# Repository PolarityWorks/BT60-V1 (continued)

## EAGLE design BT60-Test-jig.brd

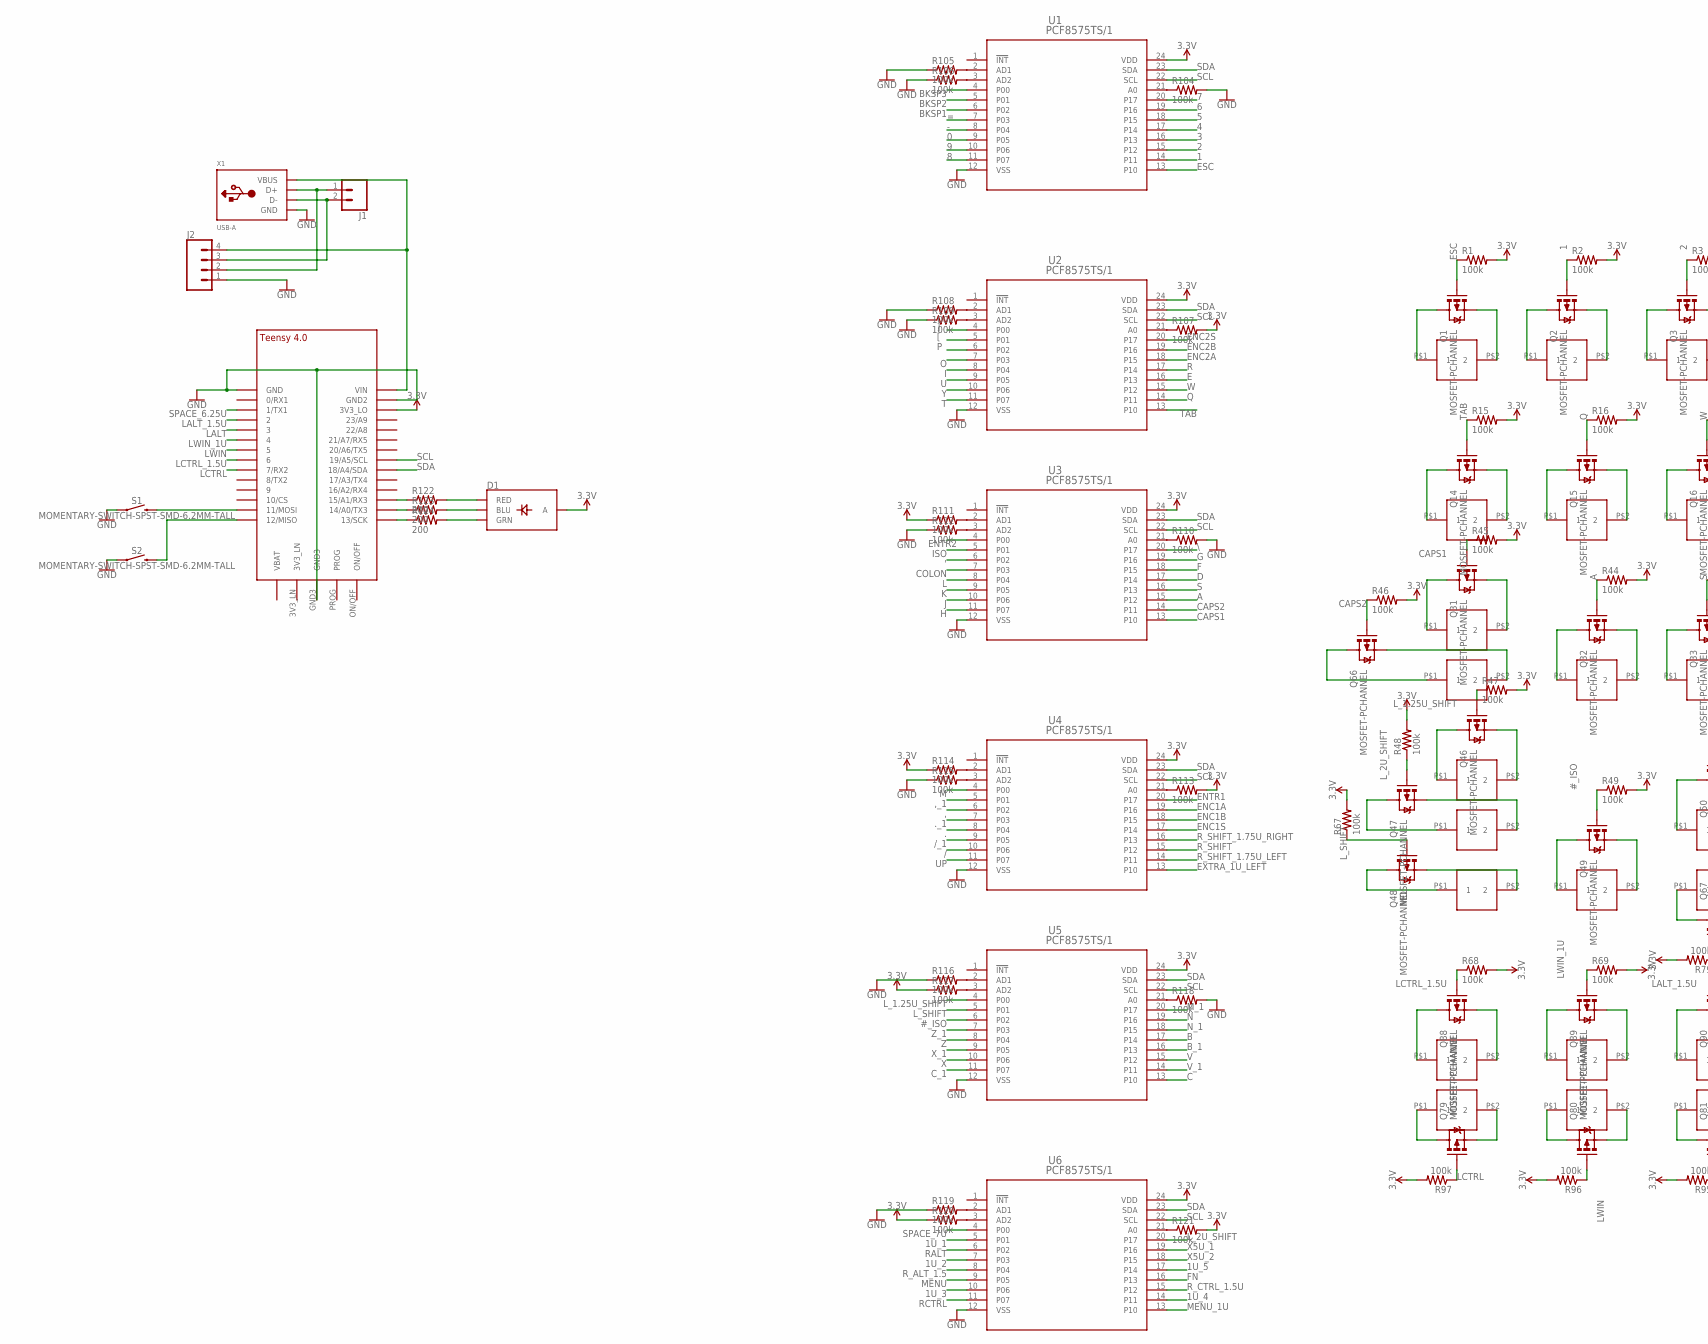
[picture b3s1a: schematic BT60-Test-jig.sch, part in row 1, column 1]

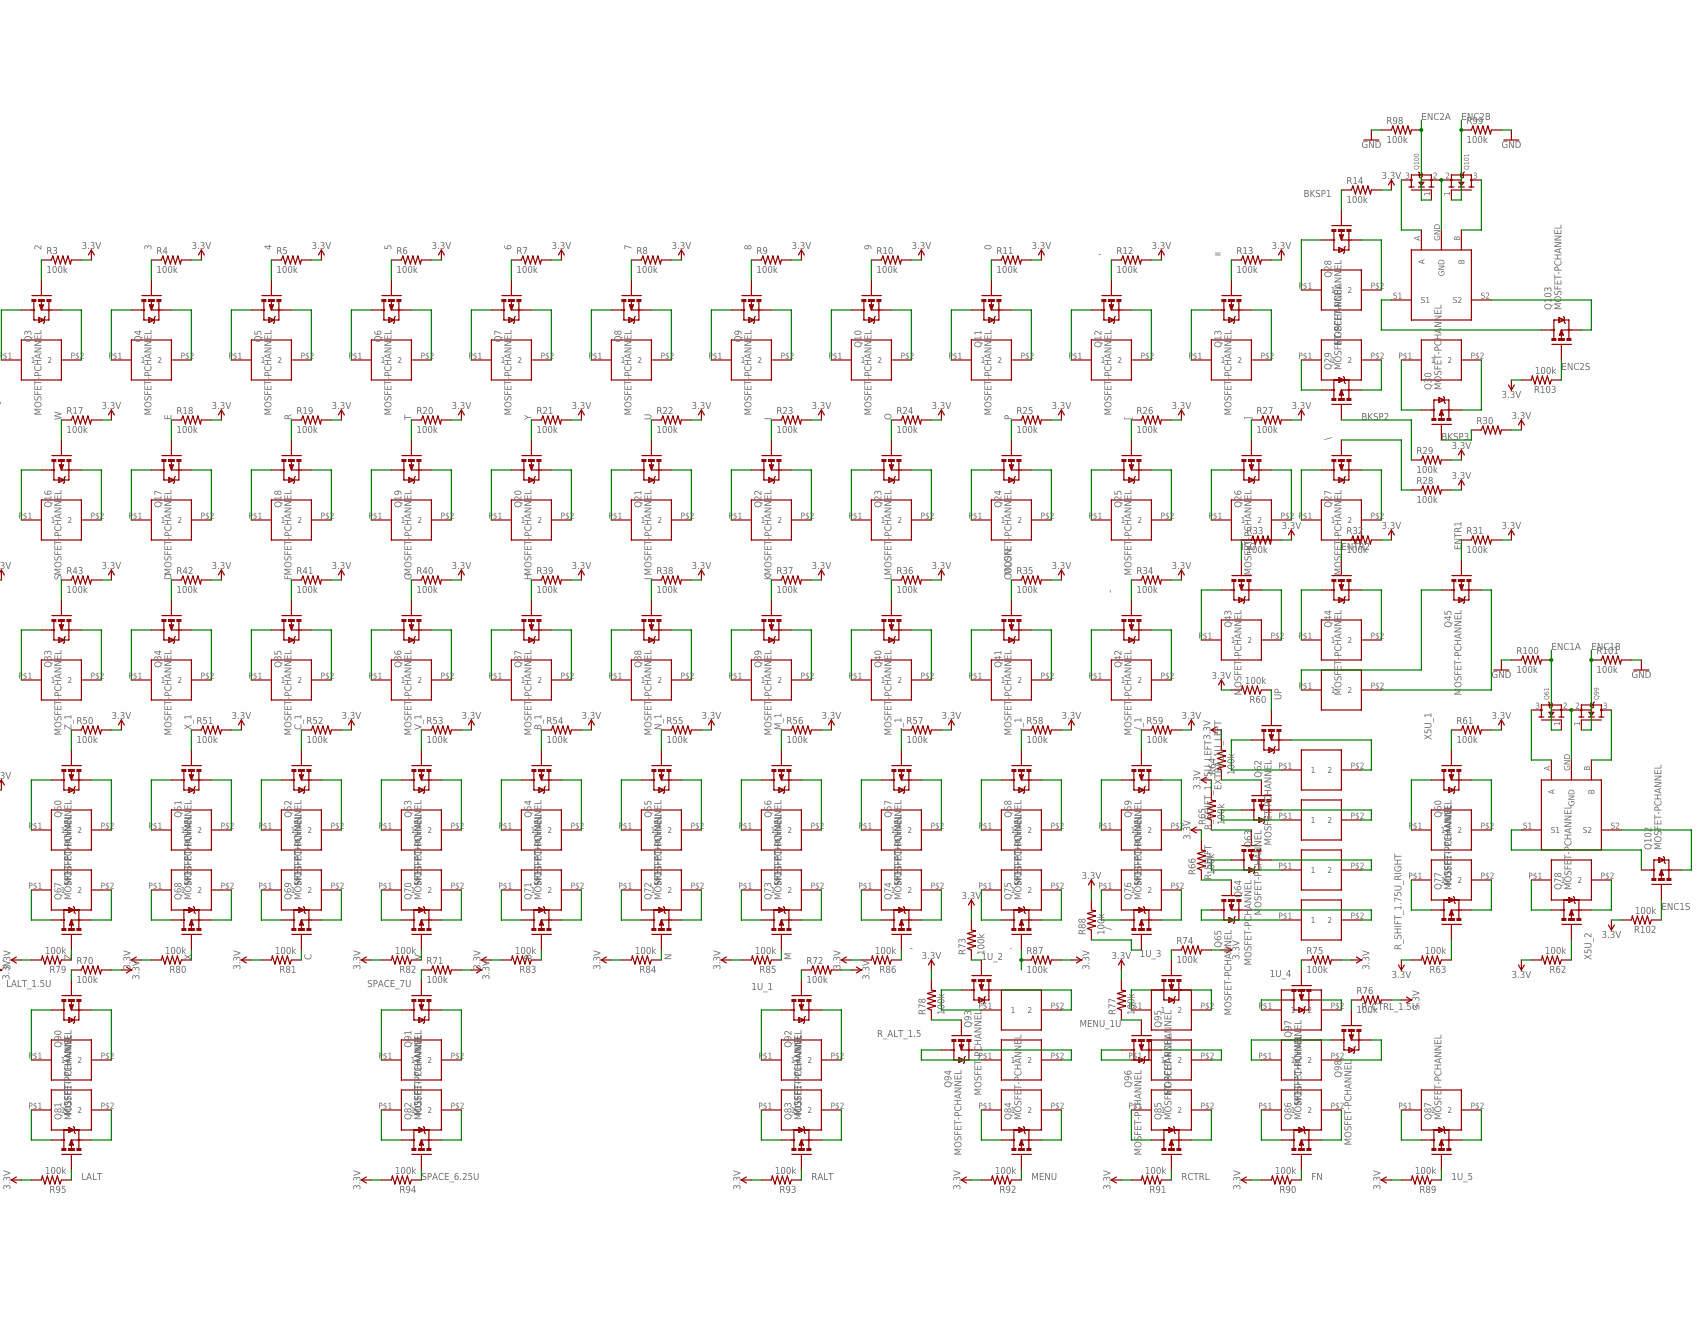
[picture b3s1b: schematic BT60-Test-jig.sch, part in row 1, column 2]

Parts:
0, 1, 1U_1, 1U_2, 1U_3, 1U_4, 1U_5, 2, 3, 4, 5, 6, 7, 8, 9, ., ._1: CHERRY-SOLDERCHERRY-TEST; CHERRY-TEST
#_ISO: CHERRY-SOLDERCHERRY-TEST; CHERRY-TEST
': CHERRY-SOLDERCHERRY-TEST; CHERRY-TEST
,: CHERRY-SOLDERCHERRY-TEST; CHERRY-TEST
,_1: CHERRY-SOLDERCHERRY-TEST; CHERRY-TEST
-: CHERRY-SOLDERCHERRY-TEST; CHERRY-TEST
/: CHERRY-SOLDERCHERRY-TEST; CHERRY-TEST
/_1: CHERRY-SOLDERCHERRY-TEST; CHERRY-TEST
=: CHERRY-SOLDERCHERRY-TEST; CHERRY-TEST
A: CHERRY-SOLDERCHERRY-TEST; CHERRY-TEST
B: CHERRY-SOLDERCHERRY-TEST; CHERRY-TEST
BS: CHERRY-SOLDERCHERRY-TEST; CHERRY-TEST
B_1: CHERRY-SOLDERCHERRY-TEST; CHERRY-TEST
C: CHERRY-SOLDERCHERRY-TEST; CHERRY-TEST
CAPS: CHERRY-SOLDERCHERRY-TEST; CHERRY-TEST
CAPS_STEP: CHERRY-SOLDERCHERRY-TEST; CHERRY-TEST
COLON: CHERRY-SOLDERCHERRY-TEST; CHERRY-TEST
C_1: CHERRY-SOLDERCHERRY-TEST; CHERRY-TEST
D: CHERRY-SOLDERCHERRY-TEST; CHERRY-TEST
D1: LED-RGB-CASMD; LED-TRICOLOR-SMD
E: CHERRY-SOLDERCHERRY-TEST; CHERRY-TEST
ENTER: CHERRY-SOLDERCHERRY-TEST; CHERRY-TEST
ESC: CHERRY-SOLDERCHERRY-TEST; CHERRY-TEST
EXTRA_1U_LEFT: CHERRY-SOLDERCHERRY-TEST; CHERRY-TEST
F: CHERRY-SOLDERCHERRY-TEST; CHERRY-TEST
FN: CHERRY-SOLDERCHERRY-TEST; CHERRY-TEST
G: CHERRY-SOLDERCHERRY-TEST; CHERRY-TEST
H: CHERRY-SOLDERCHERRY-TEST; CHERRY-TEST
I: CHERRY-SOLDERCHERRY-TEST; CHERRY-TEST
ISO_#: CHERRY-SOLDERCHERRY-TEST; CHERRY-TEST
ISO_ENTER: CHERRY-SOLDERCHERRY-TEST; CHERRY-TEST
J: CHERRY-SOLDERCHERRY-TEST; CHERRY-TEST
J1: CONN_02; 1X02
J2: CONN_041X04_NO_SILK; 1X04_NO_SILK
K: CHERRY-SOLDERCHERRY-TEST; CHERRY-TEST
L: CHERRY-SOLDERCHERRY-TEST; CHERRY-TEST
LALT: CHERRY-SOLDERCHERRY-TEST; CHERRY-TEST
LALT_1.5U: CHERRY-SOLDERCHERRY-TEST; CHERRY-TEST
LCTRL: CHERRY-SOLDERCHERRY-TEST; CHERRY-TEST
LCTRL_1.5U: CHERRY-SOLDERCHERRY-TEST; CHERRY-TEST
LWIN: CHERRY-SOLDERCHERRY-TEST; CHERRY-TEST
LWIN_1U: CHERRY-SOLDERCHERRY-TEST; CHERRY-TEST
L_1.25U_SHIFT, L_2U_SHIFT: CHERRY-SOLDERCHERRY-TEST; CHERRY-TEST
L_SHIFT: CHERRY-SOLDERCHERRY-TEST; CHERRY-TEST
M: CHERRY-SOLDERCHERRY-TEST; CHERRY-TEST
MENU: CHERRY-SOLDERCHERRY-TEST; CHERRY-TEST
MENU_1U: CHERRY-SOLDERCHERRY-TEST; CHERRY-TEST
M_1: CHERRY-SOLDERCHERRY-TEST; CHERRY-TEST
N: CHERRY-SOLDERCHERRY-TEST; CHERRY-TEST
N_1: CHERRY-SOLDERCHERRY-TEST; CHERRY-TEST
O: CHERRY-SOLDERCHERRY-TEST; CHERRY-TEST
P: CHERRY-SOLDERCHERRY-TEST; CHERRY-TEST
Q: CHERRY-SOLDERCHERRY-TEST; CHERRY-TEST
Q1, Q2, Q3, Q4, Q5, Q6, Q7, Q8, Q9, Q10, Q11, Q12, Q13, Q14, Q15, Q16, Q17, Q18, Q19, Q20, Q21, Q22, Q23, Q24, Q25, Q26, Q27, Q28, Q29, Q30, Q31, Q32, Q33, Q34, Q35, Q36, Q37, Q38, Q39, Q40, Q41, Q42, Q43, Q44, Q45, Q46, Q47, Q48, Q49, Q50, Q51, Q52, Q53, Q54, Q55, Q56, Q57, Q58, Q59, Q60, Q62, Q63, Q64, Q65, Q66, Q67, Q68, Q69, Q70, Q71, Q72, Q73, Q74, Q75, Q76, Q77, Q78, Q79, Q80, Q81, Q82, Q83, Q84, Q85, Q86, Q87, Q88, Q89, Q90, Q91, Q92, Q93, Q94, Q95, Q96, Q97, Q98, Q102, Q103: MOSFET-PCHANNEL; SOT23-3
Q61, Q99, Q100, Q101: MOSFET-NREFLOW; SOT23
R: CHERRY-SOLDERCHERRY-TEST; CHERRY-TEST
R1, R2, R3, R4, R5, R6, R7, R8, R9, R10, R11, R12, R13, R14, R15, R16, R17, R18, R19, R20, R21, R22, R23, R24, R25, R26, R27, R28, R29, R30, R31, R32, R33, R34, R35, R36, R37, R38, R39, R40, R41, R42, R43, R44, R45, R46, R47, R48, R49, R50, R51, R52, R53, R54, R55, R56, R57, R58, R59, R60, R61, R62, R63, R64, R65, R66, R67, R68, R69, R70, R71, R72, R73, R74, R75, R76, R77, R78, R79, R80, R81, R82, R83, R84, R85, R86, R87, R88, R89, R90, R91, R92, R93, R94, R95, R96, R97, R98, R99, R100, R101, R102, R103, R104, R105, R106, R107, R108, R109, R110, R111, R112, R113, R114, R115, R116, R117, R118, R119, R120, R121: 100k; 0603-R
R122, R123, R124: 200; 0603-R
RALT: CHERRY-SOLDERCHERRY-TEST; CHERRY-TEST
RCTRL: CHERRY-SOLDERCHERRY-TEST; CHERRY-TEST
R_ALT_1.5: CHERRY-SOLDERCHERRY-TEST; CHERRY-TEST
R_CTRL_1.5U: CHERRY-SOLDERCHERRY-TEST; CHERRY-TEST
R_SHIFT: CHERRY-SOLDERCHERRY-TEST; CHERRY-TEST
R_SHIFT_1.75U_LEFT, R_SHIFT_1.75U_RIGHT: CHERRY-SOLDERCHERRY-TEST; CHERRY-TEST
S: CHERRY-SOLDERCHERRY-TEST; CHERRY-TEST
S1, S2: MOMENTARY-SWITCH-SPST-SMD-6.2MM-TALL; TACTILE_SWITCH_SMD_6.2MM_TALL
SPACE_6.25U, SPACE_7U: CHERRY-SOLDERCHERRY-TEST; CHERRY-TEST
SPLIT_BS_1, SPLIT_BS_2: CHERRY-SOLDERCHERRY-TEST; CHERRY-TEST
T: CHERRY-SOLDERCHERRY-TEST; CHERRY-TEST
TAB: CHERRY-SOLDERCHERRY-TEST; CHERRY-TEST
U: CHERRY-SOLDERCHERRY-TEST; CHERRY-TEST
U1, U2, U3, U4, U5, U6: PCF8575TS/1; SOT340-1_NXP
U$1, U$3: ENCODER
U$2: TEENSY_4.0
UP: CHERRY-SOLDERCHERRY-TEST; CHERRY-TEST
V: CHERRY-SOLDERCHERRY-TEST; CHERRY-TEST
V_1: CHERRY-SOLDERCHERRY-TEST; CHERRY-TEST
W: CHERRY-SOLDERCHERRY-TEST; CHERRY-TEST
X, X5U_1, X5U_2: CHERRY-SOLDERCHERRY-TEST; CHERRY-TEST
X1: USB-A; MOLEX_480371000
X_1: CHERRY-SOLDERCHERRY-TEST; CHERRY-TEST
Y: CHERRY-SOLDERCHERRY-TEST; CHERRY-TEST
Z: CHERRY-SOLDERCHERRY-TEST; CHERRY-TEST
Z_1: CHERRY-SOLDERCHERRY-TEST; CHERRY-TEST
[: CHERRY-SOLDERCHERRY-TEST; CHERRY-TEST
\: CHERRY-SOLDERCHERRY-TEST; CHERRY-TEST
]: CHERRY-SOLDERCHERRY-TEST; CHERRY-TEST

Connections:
0: Q11.1 (G), R11.1, U1.9 (P05)
1: Q2.1 (G), R2.1, U1.14 (P11)
1U_1: Q92.1 (G), R72.1, U6.5 (P01)
1U_2: Q93.1 (G), R73.1, U6.7 (P03)
1U_3: Q95.1 (G), R74.1, U6.10 (P06)
1U_4: Q97.1 (G), R75.1, U6.14 (P11)
1U_5: Q87.1 (G), R89.1, U6.17 (P14)
2: Q3.1 (G), R3.1, U1.15 (P12)
3: Q4.1 (G), R4.1, U1.16 (P13)
3.3V: D1.A, R1.2, R2.2, R3.2, R4.2, R5.2, R6.2, R7.2, R8.2, R9.2, R10.2, R11.2, R12.2, R13.2, R14.2, R15.2, R16.2, R17.2, R18.2, R19.2, R20.2, R21.2, R22.2, R23.2, R24.2, R25.2, R26.2, R27.2, R28.2, R29.2, R30.2, R31.2, R32.2, R33.2, R34.2, R35.2, R36.2, R37.2, R38.2, R39.2, R40.2, R41.2, R42.2, R43.2, R44.2, R45.2, R46.2, R47.2, R48.2, R49.2, R50.2, R51.2, R52.2, R53.2, R54.2, R55.2, R56.2, R57.2, R58.2, R59.2, R60.2, R61.2, R62.2, R63.2, R64.2, R65.2, R66.2, R67.2, R68.2, R69.2, R70.2, R71.2, R72.2, R73.2, R74.2, R75.2, R76.2, R77.2, R78.2, R79.2, R80.2, R81.2, R82.2, R83.2, R84.2, R85.2, R86.2, R87.2, R88.2, R89.2, R90.2, R91.2, R92.2, R93.2, R94.2, R95.2, R96.2, R97.2, R102.2, R103.2, R107.2, R111.1, R113.2, R114.1, R117.1, R120.1, R121.2, U1.24 (VDD), U2.24 (VDD), U3.24 (VDD), U4.24 (VDD), U5.24 (VDD), U6.24 (VDD), U$2.3V3_LO
4: Q5.1 (G), R5.1, U1.17 (P14)
5: Q6.1 (G), R6.1, U1.18 (P15)
6: Q7.1 (G), R7.1, U1.19 (P16)
7: Q8.1 (G), R8.1, U1.20 (P17)
8: Q9.1 (G), R9.1, U1.11 (P07)
9: Q10.1 (G), R10.1, U1.10 (P06)
#_ISO: Q49.1 (G), R49.1, U5.6 (P02)
': Q42.1 (G), R34.1, U3.6 (P02)
,: Q74.1 (G), R86.1, U4.6 (P02)
,_1: Q57.1 (G), R57.1, U4.5 (P01)
-: Q12.1 (G), R12.1, U1.8 (P04)
.: Q75.1 (G), R87.1, U4.8 (P04)
._1: Q58.1 (G), R58.1, U4.7 (P03)
/: Q76.1 (G), R88.1, U4.10 (P06)
/_1: Q59.1 (G), R59.1, U4.9 (P05)
=: Q13.1 (G), R13.1, U1.7 (P03)
A: Q32.1 (G), R44.1, U3.15 (P12)
B: Q71.1 (G), R83.1, U5.17 (P14)
BKSP1: Q28.1 (G), R14.1, U1.6 (P02)
BKSP2: Q29.1 (G), R29.1, U1.5 (P01)
BKSP3: Q30.1 (G), R30.1, U1.4 (P00)
B_1: Q54.1 (G), R54.1, U5.16 (P13)
C: Q69.1 (G), R81.1, U5.13 (P10)
CAPS1: Q31.1 (G), R45.1, U3.13 (P10)
CAPS2: Q66.1 (G), R46.1, U3.14 (P11)
COLON: Q41.1 (G), R35.1, U3.7 (P03)
C_1: Q52.1 (G), R52.1, U5.11 (P07)
D: Q34.1 (G), R42.1, U3.17 (P14)
E: Q17.1 (G), R18.1, U2.16 (P13)
ENC1A: Q61.1 (G), R100.2, U4.19 (P16)
ENC1B: Q99.1 (G), R101.1, U4.18 (P15)
ENC1S: Q102.1 (G), R102.1, U4.17 (P14)
ENC2A: Q100.1 (G), R98.2, U2.18 (P15)
ENC2B: Q101.1 (G), R99.1, U2.19 (P16)
ENC2S: Q103.1 (G), R103.1, U2.20 (P17)
ENTR1: Q45.1 (G), R31.1, U4.20 (P17)
ENTR2: Q44.1 (G), R32.1, U3.4 (P00)
ESC: Q1.1 (G), R1.1, U1.13 (P10)
EXTRA_1U_LEFT: Q63.1 (G), R64.1, U4.13 (P10)
F: Q35.1 (G), R41.1, U3.18 (P15)
FN: Q86.1 (G), R90.1, U6.16 (P13)
G: Q36.1 (G), R40.1, U3.19 (P16)
GND: J2.1, R98.1, R99.2, R100.1, R101.2, R104.2, R105.1, R106.1, R108.1, R109.1, R110.2, R112.1, R115.1, R116.1, R118.2, R119.1, S1.A2 (1), S2.A2 (1), U1.12 (VSS), U2.12 (VSS), U3.12 (VSS), U4.12 (VSS), U5.12 (VSS), U6.12 (VSS), U$2.GND, U$2.GND2, U$2.GND3, X1.4 (GND)
H: Q37.1 (G), R39.1, U3.11 (P07)
I: Q22.1 (G), R23.1, U2.8 (P04)
ISO: Q43.1 (G), R33.1, U3.5 (P01)
J: Q38.1 (G), R38.1, U3.10 (P06)
K: Q39.1 (G), R37.1, U3.9 (P05)
L: Q40.1 (G), R36.1, U3.8 (P04)
LALT: Q81.1 (G), R95.1, U$2.3/CANTX (3)
LALT_1.5U: Q90.1 (G), R70.1, U$2.2
LCTRL: Q79.1 (G), R97.1, U$2.7 (7/RX2)
LCTRL_1.5U: Q88.1 (G), R68.1, U$2.6
LWIN: Q80.1 (G), R96.1, U$2.5
LWIN_1U: Q89.1 (G), R69.1, U$2.4/CANRX (4)
L_1.25U_SHIFT: Q46.1 (G), R47.1, U5.4 (P00)
L_2U_SHIFT: Q47.1 (G), R48.1, U6.20 (P17)
L_SHIFT: Q48.1 (G), R67.1, U5.5 (P01)
M: Q73.1 (G), R85.1, U4.4 (P00)
MENU: Q84.1 (G), R92.1, U6.9 (P05)
MENU_1U: Q96.1 (G), R77.1, U6.13 (P10)
M_1: Q56.1 (G), R56.1, U5.20 (P17)
N: Q72.1 (G), R84.1, U5.19 (P16)
unnamed: ESC.P$1 (1), Q1.3 (D)
unnamed: ESC.P$2 (2), Q1.2 (S)
unnamed: 1.P$1 (1), Q2.3 (D)
unnamed: 1.P$2 (2), Q2.2 (S)
unnamed: 2.P$1 (1), Q3.3 (D)
unnamed: 2.P$2 (2), Q3.2 (S)
unnamed: 3.P$1 (1), Q4.3 (D)
unnamed: 3.P$2 (2), Q4.2 (S)
unnamed: 4.P$1 (1), Q5.3 (D)
unnamed: 4.P$2 (2), Q5.2 (S)
unnamed: 5.P$1 (1), Q6.3 (D)
unnamed: 5.P$2 (2), Q6.2 (S)
unnamed: 6.P$1 (1), Q7.3 (D)
unnamed: 6.P$2 (2), Q7.2 (S)
unnamed: 7.P$1 (1), Q8.3 (D)
unnamed: 7.P$2 (2), Q8.2 (S)
unnamed: 8.P$1 (1), Q9.3 (D)
unnamed: 8.P$2 (2), Q9.2 (S)
unnamed: 9.P$1 (1), Q10.3 (D)
unnamed: 9.P$2 (2), Q10.2 (S)
unnamed: 0.P$1 (1), Q11.3 (D)
unnamed: 0.P$2 (2), Q11.2 (S)
unnamed: -.P$1 (1), Q12.3 (D)
unnamed: -.P$2 (2), Q12.2 (S)
unnamed: =.P$1 (1), Q13.3 (D)
unnamed: =.P$2 (2), Q13.2 (S)
unnamed: Q14.3 (D), TAB.P$1 (1)
unnamed: Q14.2 (S), TAB.P$2 (2)
unnamed: Q.P$1 (1), Q15.3 (D)
unnamed: Q.P$2 (2), Q15.2 (S)
unnamed: Q16.3 (D), W.P$1 (1)
unnamed: Q16.2 (S), W.P$2 (2)
unnamed: E.P$1 (1), Q17.3 (D)
unnamed: E.P$2 (2), Q17.2 (S)
unnamed: Q18.3 (D), R.P$1 (1)
unnamed: Q18.2 (S), R.P$2 (2)
unnamed: Q19.3 (D), T.P$1 (1)
unnamed: Q19.2 (S), T.P$2 (2)
unnamed: Q20.3 (D), Y.P$1 (1)
unnamed: Q20.2 (S), Y.P$2 (2)
unnamed: Q21.3 (D), U.P$1 (1)
unnamed: Q21.2 (S), U.P$2 (2)
unnamed: I.P$1 (1), Q22.3 (D)
unnamed: I.P$2 (2), Q22.2 (S)
unnamed: O.P$1 (1), Q23.3 (D)
unnamed: O.P$2 (2), Q23.2 (S)
unnamed: P.P$1 (1), Q24.3 (D)
unnamed: P.P$2 (2), Q24.2 (S)
unnamed: Q25.3 (D), [.P$1 (1)
unnamed: Q25.2 (S), [.P$2 (2)
unnamed: Q26.3 (D), ].P$1 (1)
unnamed: Q26.2 (S), ].P$2 (2)
unnamed: Q27.3 (D), \.P$1 (1)
unnamed: Q27.2 (S), \.P$2 (2)
unnamed: Q28.3 (D), SPLIT_BS_1.P$1 (1)
unnamed: Q28.2 (S), SPLIT_BS_1.P$2 (2)
unnamed: BS.P$2 (2), Q29.2 (S)
unnamed: BS.P$1 (1), Q29.3 (D)
unnamed: Q30.2 (S), SPLIT_BS_2.P$2 (2)
unnamed: Q30.3 (D), SPLIT_BS_2.P$1 (1)
unnamed: CAPS_STEP.P$1 (1), Q31.3 (D)
unnamed: CAPS_STEP.P$2 (2), Q31.2 (S)
unnamed: A.P$1 (1), Q32.3 (D)
unnamed: A.P$2 (2), Q32.2 (S)
unnamed: Q33.3 (D), S.P$1 (1)
unnamed: Q33.2 (S), S.P$2 (2)
unnamed: D.P$1 (1), Q34.3 (D)
unnamed: D.P$2 (2), Q34.2 (S)
unnamed: F.P$1 (1), Q35.3 (D)
unnamed: F.P$2 (2), Q35.2 (S)
unnamed: G.P$1 (1), Q36.3 (D)
unnamed: G.P$2 (2), Q36.2 (S)
unnamed: H.P$1 (1), Q37.3 (D)
unnamed: H.P$2 (2), Q37.2 (S)
unnamed: J.P$1 (1), Q38.3 (D)
unnamed: J.P$2 (2), Q38.2 (S)
unnamed: K.P$1 (1), Q39.3 (D)
unnamed: K.P$2 (2), Q39.2 (S)
unnamed: L.P$1 (1), Q40.3 (D)
unnamed: L.P$2 (2), Q40.2 (S)
unnamed: COLON.P$1 (1), Q41.3 (D)
unnamed: COLON.P$2 (2), Q41.2 (S)
unnamed: '.P$1 (1), Q42.3 (D)
unnamed: '.P$2 (2), Q42.2 (S)
unnamed: ISO_#.P$1 (1), Q43.3 (D)
unnamed: ISO_#.P$2 (2), Q43.2 (S)
unnamed: ISO_ENTER.P$1 (1), Q44.3 (D)
unnamed: ISO_ENTER.P$2 (2), Q44.2 (S)
unnamed: ENTER.P$1 (1), Q45.3 (D)
unnamed: ENTER.P$2 (2), Q45.2 (S)
unnamed: L_1.25U_SHIFT.P$1 (1), Q46.3 (D)
unnamed: L_1.25U_SHIFT.P$2 (2), Q46.2 (S)
unnamed: L_2U_SHIFT.P$1 (1), Q47.3 (D)
unnamed: L_2U_SHIFT.P$2 (2), Q47.2 (S)
unnamed: L_SHIFT.P$1 (1), Q48.3 (D)
unnamed: L_SHIFT.P$2 (2), Q48.2 (S)
unnamed: #_ISO.P$1 (1), Q49.3 (D)
unnamed: #_ISO.P$2 (2), Q49.2 (S)
unnamed: Q50.3 (D), Z_1.P$1 (1)
unnamed: Q50.2 (S), Z_1.P$2 (2)
unnamed: Q51.3 (D), X_1.P$1 (1)
unnamed: Q51.2 (S), X_1.P$2 (2)
unnamed: C_1.P$1 (1), Q52.3 (D)
unnamed: C_1.P$2 (2), Q52.2 (S)
unnamed: Q53.3 (D), V_1.P$1 (1)
unnamed: Q53.2 (S), V_1.P$2 (2)
unnamed: B_1.P$1 (1), Q54.3 (D)
unnamed: B_1.P$2 (2), Q54.2 (S)
unnamed: N_1.P$1 (1), Q55.3 (D)
unnamed: N_1.P$2 (2), Q55.2 (S)
unnamed: M_1.P$1 (1), Q56.3 (D)
unnamed: M_1.P$2 (2), Q56.2 (S)
unnamed: ,_1.P$1 (1), Q57.3 (D)
unnamed: ,_1.P$2 (2), Q57.2 (S)
unnamed: ._1.P$1 (1), Q58.3 (D)
unnamed: ._1.P$2 (2), Q58.2 (S)
unnamed: /_1.P$1 (1), Q59.3 (D)
unnamed: /_1.P$2 (2), Q59.2 (S)
unnamed: Q60.3 (D), X5U_1.P$1 (1)
unnamed: Q60.2 (S), X5U_1.P$2 (2)
unnamed: Q61.2 (S), Q99.2 (S), U$3.GND
unnamed: Q61.3 (D), U$3.A
unnamed: Q62.3 (D), UP.P$1 (1)
unnamed: Q62.2 (S), UP.P$2 (2)
unnamed: EXTRA_1U_LEFT.P$1 (1), Q63.3 (D)
unnamed: EXTRA_1U_LEFT.P$2 (2), Q63.2 (S)
unnamed: Q64.3 (D), R_SHIFT_1.75U_LEFT.P$1 (1)
unnamed: Q64.2 (S), R_SHIFT_1.75U_LEFT.P$2 (2)
unnamed: Q65.3 (D), R_SHIFT.P$1 (1)
unnamed: Q65.2 (S), R_SHIFT.P$2 (2)
unnamed: CAPS.P$1 (1), Q66.3 (D)
unnamed: CAPS.P$2 (2), Q66.2 (S)
unnamed: Q67.2 (S), Z.P$2 (2)
unnamed: Q67.3 (D), Z.P$1 (1)
unnamed: Q68.2 (S), X.P$2 (2)
unnamed: Q68.3 (D), X.P$1 (1)
unnamed: C.P$2 (2), Q69.2 (S)
unnamed: C.P$1 (1), Q69.3 (D)
unnamed: Q70.2 (S), V.P$2 (2)
unnamed: Q70.3 (D), V.P$1 (1)
unnamed: B.P$2 (2), Q71.2 (S)
unnamed: B.P$1 (1), Q71.3 (D)
unnamed: N.P$2 (2), Q72.2 (S)
unnamed: N.P$1 (1), Q72.3 (D)
unnamed: M.P$2 (2), Q73.2 (S)
unnamed: M.P$1 (1), Q73.3 (D)
unnamed: ,.P$2 (2), Q74.2 (S)
unnamed: ,.P$1 (1), Q74.3 (D)
unnamed: ..P$2 (2), Q75.2 (S)
unnamed: ..P$1 (1), Q75.3 (D)
unnamed: /.P$2 (2), Q76.2 (S)
unnamed: /.P$1 (1), Q76.3 (D)
unnamed: Q77.2 (S), R_SHIFT_1.75U_RIGHT.P$2 (2)
unnamed: Q77.3 (D), R_SHIFT_1.75U_RIGHT.P$1 (1)
unnamed: Q78.2 (S), X5U_2.P$2 (2)
unnamed: Q78.3 (D), X5U_2.P$1 (1)
unnamed: LCTRL.P$2 (2), Q79.2 (S)
unnamed: LCTRL.P$1 (1), Q79.3 (D)
unnamed: LWIN.P$2 (2), Q80.2 (S)
unnamed: LWIN.P$1 (1), Q80.3 (D)
unnamed: LALT.P$2 (2), Q81.2 (S)
unnamed: LALT.P$1 (1), Q81.3 (D)
unnamed: Q82.2 (S), SPACE_6.25U.P$2 (2)
unnamed: Q82.3 (D), SPACE_6.25U.P$1 (1)
unnamed: Q83.2 (S), RALT.P$2 (2)
unnamed: Q83.3 (D), RALT.P$1 (1)
unnamed: MENU.P$2 (2), Q84.2 (S)
unnamed: MENU.P$1 (1), Q84.3 (D)
unnamed: Q85.2 (S), RCTRL.P$2 (2)
unnamed: Q85.3 (D), RCTRL.P$1 (1)
unnamed: FN.P$2 (2), Q86.2 (S)
unnamed: FN.P$1 (1), Q86.3 (D)
unnamed: 1U_5.P$2 (2), Q87.2 (S)
unnamed: 1U_5.P$1 (1), Q87.3 (D)
unnamed: LCTRL_1.5U.P$1 (1), Q88.3 (D)
unnamed: LCTRL_1.5U.P$2 (2), Q88.2 (S)
unnamed: LWIN_1U.P$1 (1), Q89.3 (D)
unnamed: LWIN_1U.P$2 (2), Q89.2 (S)
unnamed: LALT_1.5U.P$1 (1), Q90.3 (D)
unnamed: LALT_1.5U.P$2 (2), Q90.2 (S)
unnamed: Q91.3 (D), SPACE_7U.P$1 (1)
unnamed: Q91.2 (S), SPACE_7U.P$2 (2)
unnamed: 1U_1.P$1 (1), Q92.3 (D)
unnamed: 1U_1.P$2 (2), Q92.2 (S)
unnamed: 1U_2.P$1 (1), Q93.3 (D)
unnamed: 1U_2.P$2 (2), Q93.2 (S)
unnamed: Q94.3 (D), R_ALT_1.5.P$1 (1)
unnamed: Q94.2 (S), R_ALT_1.5.P$2 (2)
unnamed: 1U_3.P$1 (1), Q95.3 (D)
unnamed: 1U_3.P$2 (2), Q95.2 (S)
unnamed: MENU_1U.P$1 (1), Q96.3 (D)
unnamed: MENU_1U.P$2 (2), Q96.2 (S)
unnamed: 1U_4.P$1 (1), Q97.3 (D)
unnamed: 1U_4.P$2 (2), Q97.2 (S)
unnamed: Q98.3 (D), R_CTRL_1.5U.P$1 (1)
unnamed: Q98.2 (S), R_CTRL_1.5U.P$2 (2)
unnamed: Q99.3 (D), U$3.B
unnamed: Q100.2 (S), Q101.2 (S), U$1.GND
unnamed: Q100.3 (D), U$1.A
unnamed: Q101.3 (D), U$1.B
unnamed: Q103.3 (D), U$1.S1
unnamed: Q103.2 (S), U$1.S2
unnamed: Q102.3 (D), U$3.S1
unnamed: Q102.2 (S), U$3.S2
unnamed: R104.1, U1.21 (A0)
unnamed: R105.2, U1.2 (AD1)
unnamed: R106.2, U1.3 (AD2)
unnamed: R107.1, U2.21 (A0)
unnamed: R108.2, U2.2 (AD1)
unnamed: R109.2, U2.3 (AD2)
unnamed: R111.2, U3.2 (AD1)
unnamed: R112.2, U3.3 (AD2)
unnamed: R110.1, U3.21 (A0)
unnamed: R113.1, U4.21 (A0)
unnamed: R114.2, U4.2 (AD1)
unnamed: R115.2, U4.3 (AD2)
unnamed: R116.2, U5.2 (AD1)
unnamed: R117.2, U5.3 (AD2)
unnamed: R118.1, U5.21 (A0)
unnamed: J2.4, U$2.VIN, X1.1 (VBUS)
unnamed: J1.1, J2.2, X1.3 (D+)
unnamed: J1.2, J2.3, X1.2 (D-)
unnamed: D1.R (RED), R122.2
unnamed: D1.B (BLU), R123.2
unnamed: D1.G (GRN), R124.2
unnamed: R124.1, U$2.13/SCK
unnamed: R123.1, U$2.14/A0 (14/A0/TX3)
unnamed: R122.1, U$2.15/A1 (15/A1/RX3)
unnamed: S1.B2 (2), U$2.11/MOSI
unnamed: S2.B2 (2), U$2.12/MISO
unnamed: R119.2, U6.2 (AD1)
unnamed: R120.2, U6.3 (AD2)
unnamed: R121.1, U6.21 (A0)
N_1: Q55.1 (G), R55.1, U5.18 (P15)
O: Q23.1 (G), R24.1, U2.7 (P03)
P: Q24.1 (G), R25.1, U2.6 (P02)
Q: Q15.1 (G), R16.1, U2.14 (P11)
R: Q18.1 (G), R19.1, U2.17 (P14)
RALT: Q83.1 (G), R93.1, U6.6 (P02)
RCTRL: Q85.1 (G), R91.1, U6.11 (P07)
R_ALT_1.5: Q94.1 (G), R78.1, U6.8 (P04)
R_CTRL_1.5U: Q98.1 (G), R76.1, U6.15 (P12)
R_SHIFT: Q65.1 (G), R66.1, U4.15 (P12)
R_SHIFT_1.75U_LEFT: Q64.1 (G), R65.1, U4.14 (P11)
R_SHIFT_1.75U_RIGHT: Q77.1 (G), R63.1, U4.16 (P13)
S: Q33.1 (G), R43.1, U3.16 (P13)
SCL: U1.22 (SCL), U2.22 (SCL), U3.22 (SCL), U4.22 (SCL), U5.22 (SCL), U6.22 (SCL), U$2.19/A5/SCL
SDA: U1.23 (SDA), U2.23 (SDA), U3.23 (SDA), U4.23 (SDA), U5.23 (SDA), U6.23 (SDA), U$2.18/A4/SDA
SPACE_6.25U: Q82.1 (G), R94.1, U$2.1/TX (1/TX1)
SPACE_7U: Q91.1 (G), R71.1, U6.4 (P00)
T: Q19.1 (G), R20.1, U2.11 (P07)
TAB: Q14.1 (G), R15.1, U2.13 (P10)
U: Q21.1 (G), R22.1, U2.9 (P05)
UP: Q62.1 (G), R60.1, U4.11 (P07)
V: Q70.1 (G), R82.1, U5.15 (P12)
V_1: Q53.1 (G), R53.1, U5.14 (P11)
W: Q16.1 (G), R17.1, U2.15 (P12)
X: Q68.1 (G), R80.1, U5.10 (P06)
X5U_1: Q60.1 (G), R61.1, U6.19 (P16)
X5U_2: Q78.1 (G), R62.1, U6.18 (P15)
X_1: Q51.1 (G), R51.1, U5.9 (P05)
Y: Q20.1 (G), R21.1, U2.10 (P06)
Z: Q67.1 (G), R79.1, U5.8 (P04)
Z_1: Q50.1 (G), R50.1, U5.7 (P03)
[: Q25.1 (G), R26.1, U2.5 (P01)
\: Q27.1 (G), R28.1, U3.20 (P17)
]: Q26.1 (G), R27.1, U2.4 (P00)

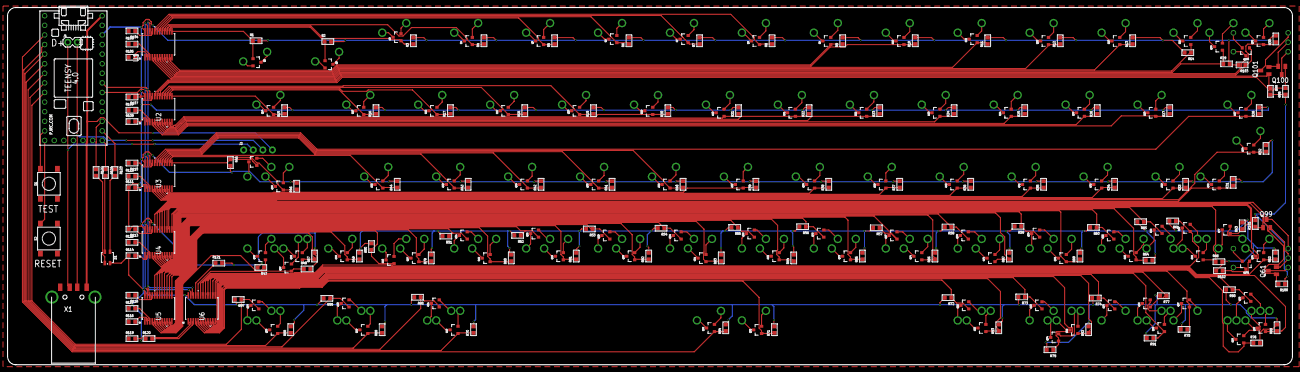
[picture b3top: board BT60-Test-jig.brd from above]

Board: 2 copper layers, 340.3 x 94.6 mm, 339 parts (0 on the bottom side), 340 nets.

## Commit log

2020-12-14 initial upload
2020-12-27 tweaks and checks
2020-12-30 tweaksa for erc
2021-02-05 new board
2021-02-26 latest revision
2021-02-26 library updates
2021-02-26 Autosave purge
2021-03-04 soldered version
2021-05-04 hmmm
2021-06-02 updatyes
2021-06-14 bt60 test jig upload
2021-08-03 Final update before release
2021-11-23 Tidy up for release
2021-11-23 further release tweaks
2021-12-30 Schematic Update
2022-02-08 Cleanup
2022-02-08 Added Layout PDF
